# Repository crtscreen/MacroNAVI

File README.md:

# MacroNAVI

MacroNAVI is a simple 3-key macropad with an OLED display, and uses KMK firmware. The reasoning for its lack of features is that I want it to serve as something small that I can take with me. The main standout is supposed to be the open case, which exposes the PCB, showing the controller and some cool art on the PCB. I built this macropad for [Hackpad](https://hackpad.hackclub.com/), as part of [Stardance](https://stardance.hackclub.com/).

## Features

- Three MX switches
- 128x32 OLED Display
- Exposed case
- KMK firmware

## Case

It has two case pieces, fitted together with four (4) screws and heat-set inserts. I used FreeCAD for the case design because I dislike Fusion360. The editable FreeCAD files, complete STEP assembly, and printable STLs are in `cad/`.

## PCB

PCB made using KiCad. The source files and project libraries are in `pcb/`, and manufacturing files are packaged in `pcb/gerbers.zip`.

## Schematic

Here's a screenshot of the schematic:

## Firmware
The firmware is in `firmware/main.py` and uses KMK on CircuitPython.
| Key | Current assignment |
| ----- | ---------------- |
| Left | F13 |
| Middle | F14 |
| Right | F15 |

The OLED is configured to display "COPLAND OS" and the key assignments. When I actually build it I will probably remap these keys to be media controls.

## Credits
Huge thanks to the [Alex Ren](https://github.com/qcoral) at Hackpad for running this awesome YSWS project.

## BOM
| Part | Quantity |
| --- | --- |
| Seeed Studio XIAO RP2040 | 1 |
| MX-style switches | 3 |
| White blank DSA keycaps, 1u | 3 |
| 0.91-inch 128×32 I²C OLED, GND-VCC-SCL-SDA | 1 |
| 1×7 male pin headers, 2.54 mm pitch | 2 |
| M3×16 mm screws | 4 |
| M3 heat-set inserts, 5 mm OD × 4 mm long | 4 |
| Custom MacroNAVI PCB | 1 |
| 3D-printed top plate | 1 |
| 3D-printed bottom case | 1 |

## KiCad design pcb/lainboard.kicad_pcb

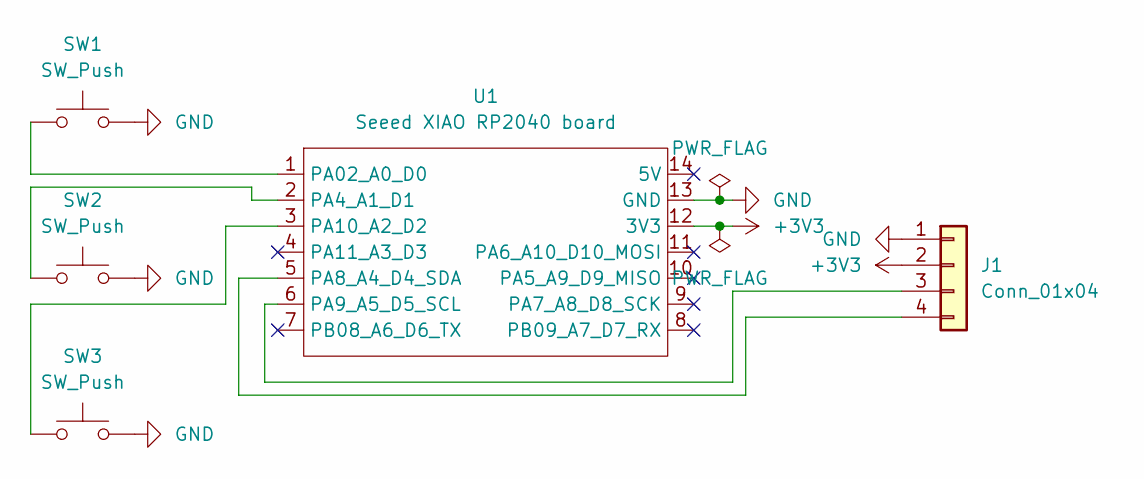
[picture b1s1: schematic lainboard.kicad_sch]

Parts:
J1: Conn_01x04; SSD1306-0.91-OLED-4pin-128x32
SW1, SW2, SW3: SW_Push; SW_Cherry_MX_1.00u_PCB
U1: Seeed XIAO RP2040 board; XIAO-RP2040-DIP

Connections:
+3V3: J1.2, U1.12 (3V3)
GND: J1.1, SW1.2, SW2.2, SW3.2, U1.13 (GND)
unnamed: J1.3, U1.6 (PA9_A5_D5_SCL)
unnamed: J1.4, U1.5 (PA8_A4_D4_SDA)
unnamed: SW1.1, U1.1 (PA02_A0_D0)
unnamed: SW2.1, U1.2 (PA4_A1_D1)
unnamed: SW3.1, U1.3 (PA10_A2_D2)

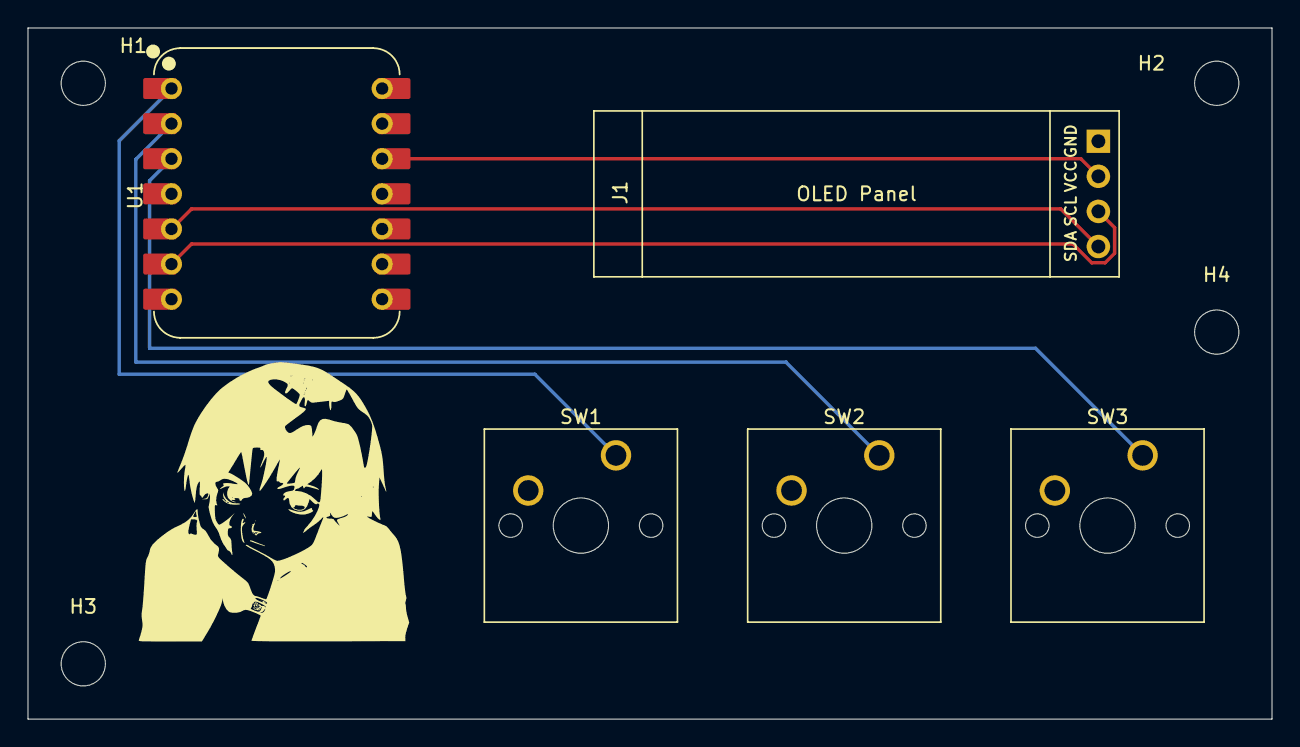
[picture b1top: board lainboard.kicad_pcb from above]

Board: 2 copper layers, 90.0 x 50.0 mm, 10 parts (0 on the bottom side), 7 nets.

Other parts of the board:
H1, H2, H3, H4: MountingHole_3.2mm_M3
LainArt: LOGO; LainArt
